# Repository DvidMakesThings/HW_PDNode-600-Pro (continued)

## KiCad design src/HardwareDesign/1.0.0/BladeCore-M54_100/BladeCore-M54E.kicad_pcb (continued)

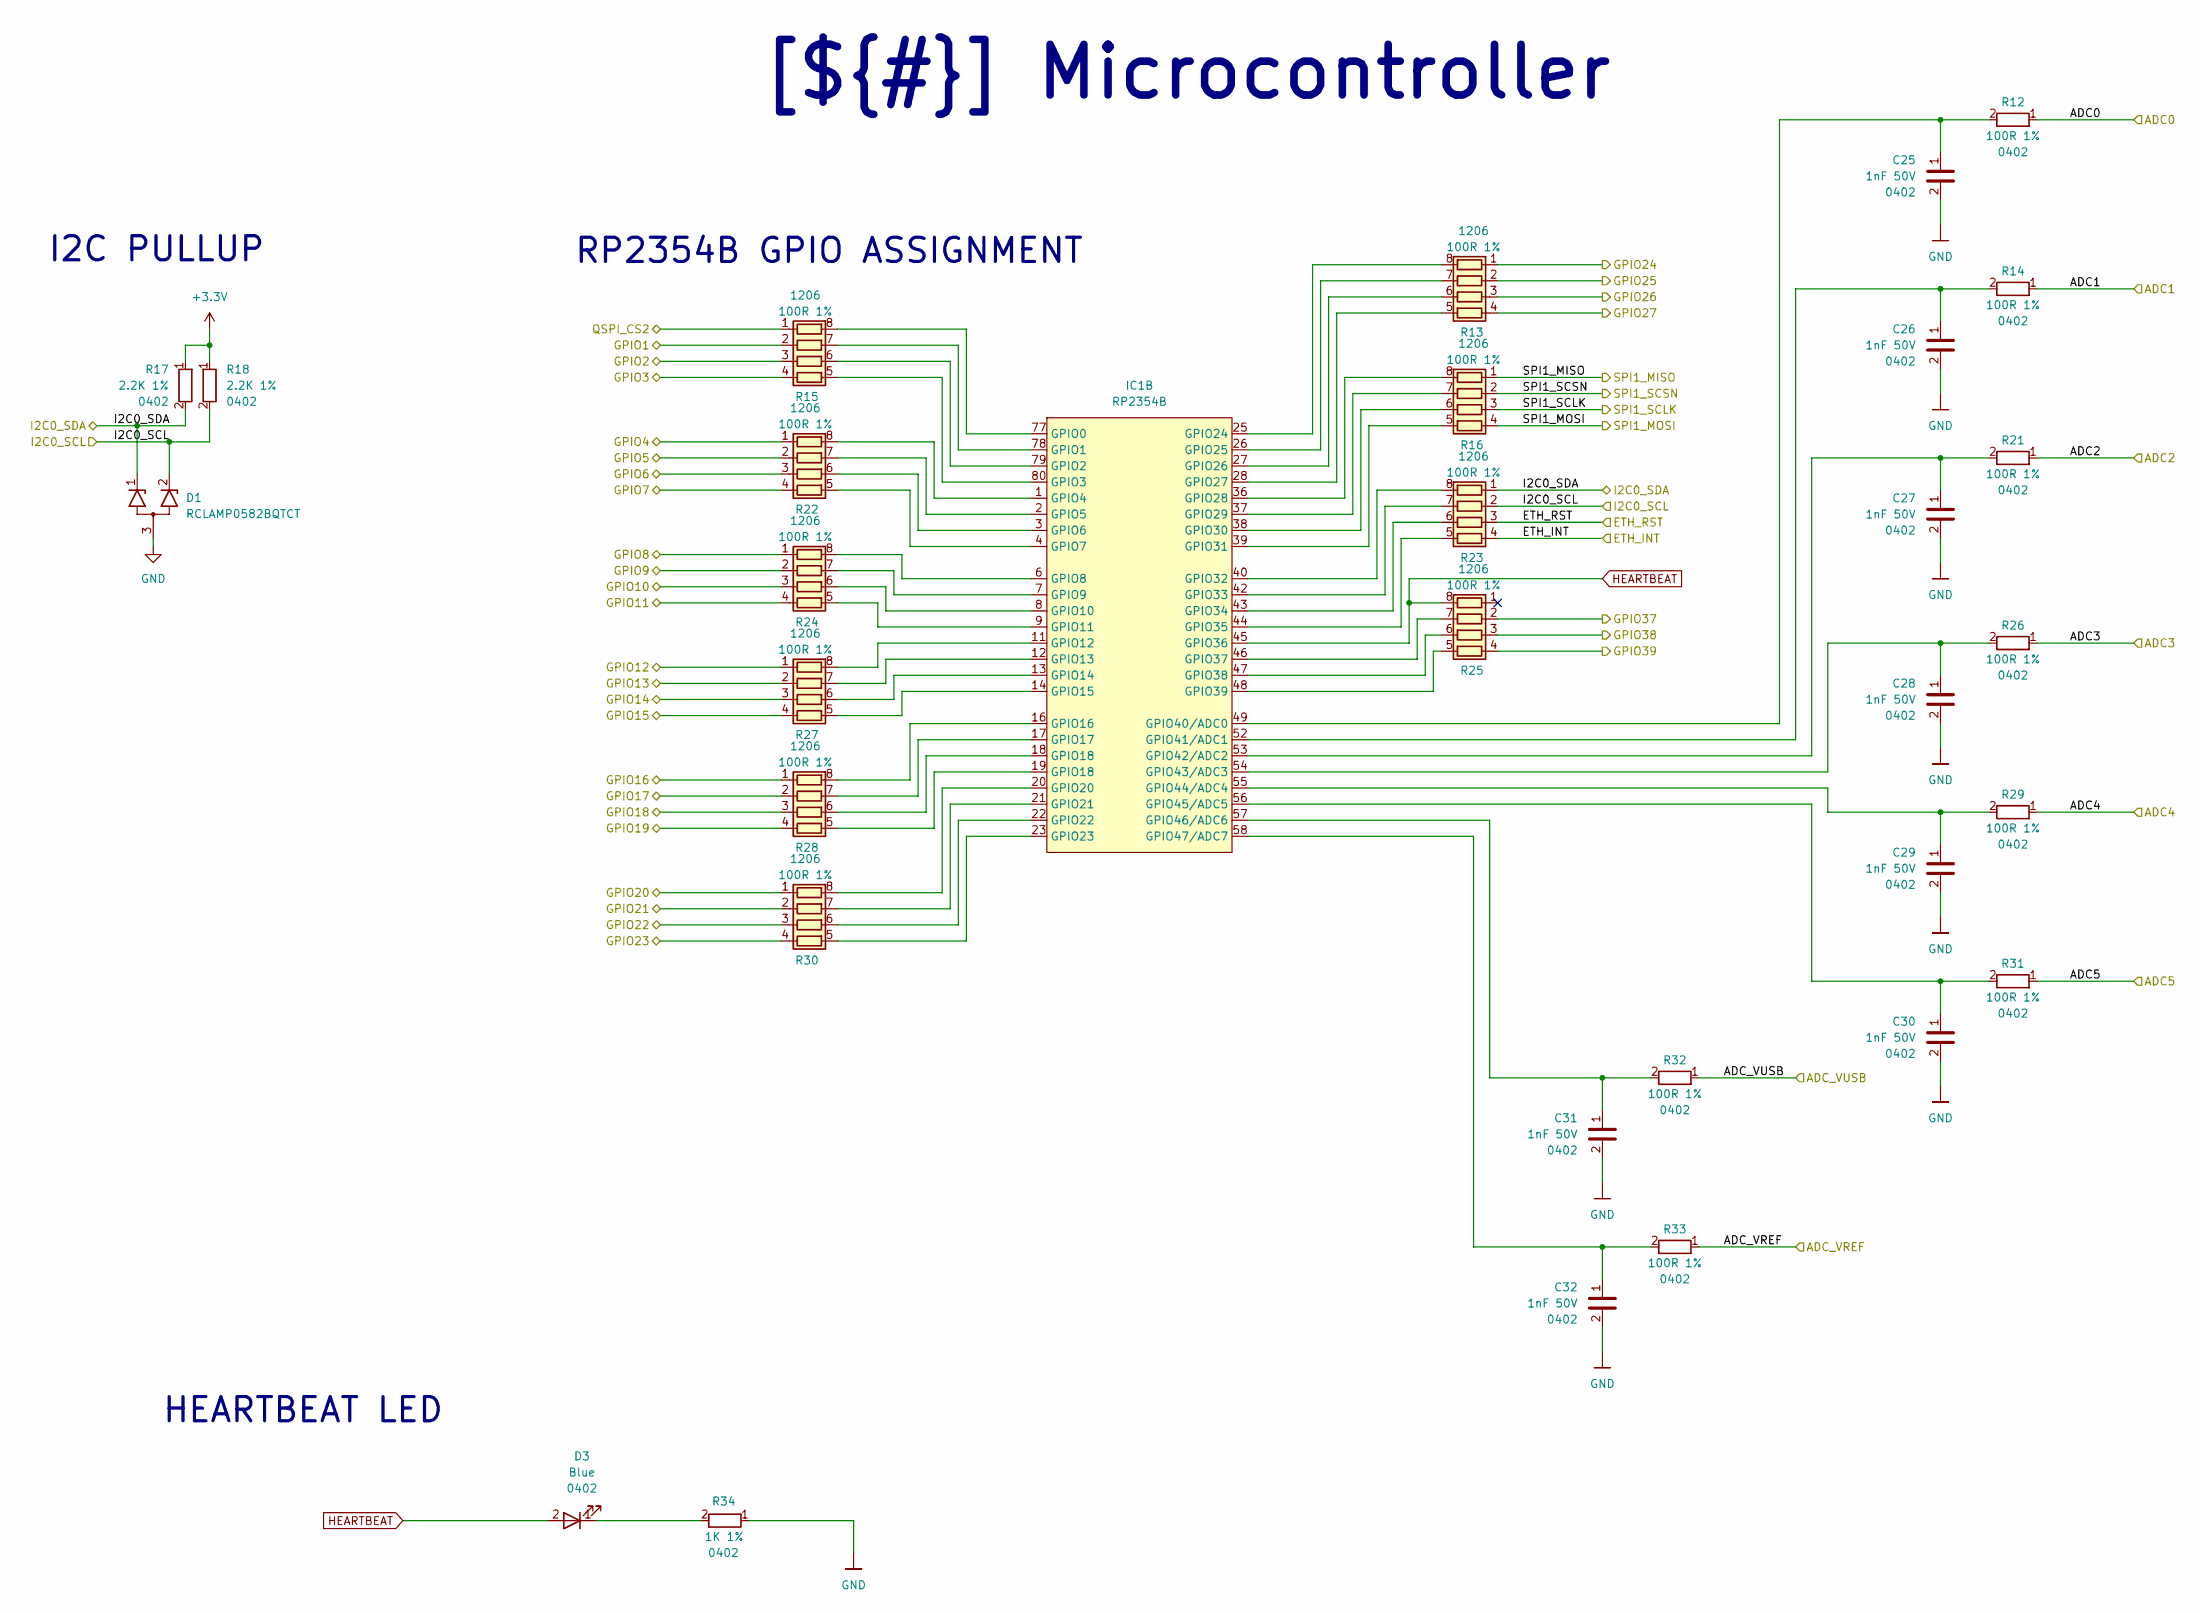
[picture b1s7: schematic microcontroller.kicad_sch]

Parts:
C25, C26, C27, C28, C29, C30, C31, C32: 1nF 50V; C_0402_1005Metric; LCSC_PART C14442
D1: RCLAMP0582BQTCT; SOT-416; MPN RCLAMP0582BQTCT; LCSC_PART C841193
D3: Blue; LED_0402_1005Metric; MPN XL-1005UBC; LCSC_PART C22355736
IC1: RP2354B; QFN80_10x10; MPN RP2354B; LCSC_PART C39843328
R12, R14, R21, R26, R29, R31, R32, R33: 100R 1%; R_0402_1005Metric; LCSC_PART C25076
R13, R15, R16, R22, R23, R24, R25, R27, R28, R30: 100R 1%; R_Array_Convex_4x0603; MPN YC164-FR-07100RL; LCSC_PART C136838
R17, R18: 2.2K 1%; R_0402_1005Metric; LCSC_PART C25879
R34: 1K 1%; R_0402_1005Metric; LCSC_PART C11702

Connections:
+3.3V: R17.1, R18.1; also elsewhere on the board
/Project Architecture/ADC0: R12.1; also elsewhere on the board
/Project Architecture/ADC1: R14.1; also elsewhere on the board
/Project Architecture/ADC2: R21.1; also elsewhere on the board
/Project Architecture/ADC3: R26.1; also elsewhere on the board
/Project Architecture/ADC4: R29.1; also elsewhere on the board
/Project Architecture/ADC5: R31.1; also elsewhere on the board
/Project Architecture/Ethernet Interface/ETH_INT: R23.4 (R14); also elsewhere on the board
/Project Architecture/Ethernet Interface/ETH_RST: R23.3 (R13); also elsewhere on the board
/Project Architecture/Ethernet Interface/SPI1_MISO: R16.1 (R11); also elsewhere on the board
/Project Architecture/Ethernet Interface/SPI1_MOSI: R16.4 (R14); also elsewhere on the board
/Project Architecture/Ethernet Interface/SPI1_SCLK: R16.3 (R13); also elsewhere on the board
/Project Architecture/Ethernet Interface/SPI1_SCSN: R16.2 (R12); also elsewhere on the board
/Project Architecture/GPIO0: R15.1 (R11); also elsewhere on the board
/Project Architecture/GPIO1: R15.2 (R12); also elsewhere on the board
/Project Architecture/GPIO2: R15.3 (R13); also elsewhere on the board
/Project Architecture/GPIO3: R15.4 (R14); also elsewhere on the board
/Project Architecture/GPIO4: R22.1 (R11); also elsewhere on the board
/Project Architecture/GPIO5: R22.2 (R12); also elsewhere on the board
/Project Architecture/GPIO6: R22.3 (R13); also elsewhere on the board
/Project Architecture/GPIO7: R22.4 (R14); also elsewhere on the board
/Project Architecture/GPIO8: R24.1 (R11); also elsewhere on the board
/Project Architecture/GPIO9: R24.2 (R12); also elsewhere on the board
/Project Architecture/GPIO10: R24.3 (R13); also elsewhere on the board
/Project Architecture/GPIO11: R24.4 (R14); also elsewhere on the board
/Project Architecture/GPIO12: R27.1 (R11); also elsewhere on the board
/Project Architecture/GPIO13: R27.2 (R12); also elsewhere on the board
/Project Architecture/GPIO14: R27.3 (R13); also elsewhere on the board
/Project Architecture/GPIO15: R27.4 (R14); also elsewhere on the board
/Project Architecture/GPIO16: R28.1 (R11); also elsewhere on the board
/Project Architecture/GPIO17: R28.2 (R12); also elsewhere on the board
/Project Architecture/GPIO18: R28.3 (R13); also elsewhere on the board
/Project Architecture/GPIO19: R28.4 (R14); also elsewhere on the board
/Project Architecture/GPIO20: R30.1 (R11); also elsewhere on the board
/Project Architecture/GPIO21: R30.2 (R12); also elsewhere on the board
/Project Architecture/GPIO22: R30.3 (R13); also elsewhere on the board
/Project Architecture/GPIO23: R30.4 (R14); also elsewhere on the board
/Project Architecture/GPIO24: R13.1 (R11); also elsewhere on the board
/Project Architecture/GPIO25: R13.2 (R12); also elsewhere on the board
/Project Architecture/GPIO26: R13.3 (R13); also elsewhere on the board
/Project Architecture/GPIO27: R13.4 (R14); also elsewhere on the board
/Project Architecture/Microcontroller Peripherals/ADC_VREF: R33.1; also elsewhere on the board
/Project Architecture/Microcontroller Peripherals/I2C0_SCL: D1.2 (K2), R18.2, R23.2 (R12); also elsewhere on the board
/Project Architecture/Microcontroller Peripherals/I2C0_SDA: D1.1 (K1), R17.2, R23.1 (R11); also elsewhere on the board
/Project Architecture/Microcontroller/ADC_VUSB: R32.1; also elsewhere on the board
/Project Architecture/Microcontroller/GPIO37: R25.2 (R12)
/Project Architecture/Microcontroller/GPIO38: R25.3 (R13)
/Project Architecture/Microcontroller/GPIO39: R25.4 (R14)
GND: C25.2, C26.2, C27.2, C28.2, C29.2, C30.2, C31.2, C32.2, D1.3 (A), R34.1; also elsewhere on the board
HEARTBEAT: D3.2, IC1.45 (GPIO36), R25.8 (R12)
unnamed: D3.1, R34.2
unnamed: IC1.77 (GPIO0), R15.8 (R12)
unnamed: IC1.78 (GPIO1), R15.7 (R22)
unnamed: IC1.79 (GPIO2), R15.6 (R23)
unnamed: IC1.80 (GPIO3), R15.5 (R24)
unnamed: IC1.1 (GPIO4), R22.8 (R12)
unnamed: IC1.2 (GPIO5), R22.7 (R22)
unnamed: IC1.3 (GPIO6), R22.6 (R23)
unnamed: IC1.4 (GPIO7), R22.5 (R24)
unnamed: IC1.6 (GPIO8), R24.8 (R12)
unnamed: IC1.7 (GPIO9), R24.7 (R22)
unnamed: IC1.8 (GPIO10), R24.6 (R23)
unnamed: IC1.9 (GPIO11), R24.5 (R24)
unnamed: IC1.11 (GPIO12), R27.8 (R12)
unnamed: IC1.12 (GPIO13), R27.7 (R22)
unnamed: IC1.13 (GPIO14), R27.6 (R23)
unnamed: IC1.14 (GPIO15), R27.5 (R24)
unnamed: IC1.16 (GPIO16), R28.8 (R12)
unnamed: IC1.17 (GPIO17), R28.7 (R22)
unnamed: IC1.20 (GPIO20), R30.8 (R12)
unnamed: IC1.21 (GPIO21), R30.7 (R22)
unnamed: IC1.22 (GPIO22), R30.6 (R23)
unnamed: IC1.23 (GPIO23), R30.5 (R24)
unnamed: IC1.25 (GPIO24), R13.8 (R12)
unnamed: IC1.26 (GPIO25), R13.7 (R22)
unnamed: IC1.27 (GPIO26), R13.6 (R23)
unnamed: IC1.28 (GPIO27), R13.5 (R24)
unnamed: IC1.36 (GPIO28), R16.8 (R12)
unnamed: IC1.37 (GPIO29), R16.7 (R22)
unnamed: IC1.38 (GPIO30), R16.6 (R23)
unnamed: IC1.39 (GPIO31), R16.5 (R24)
unnamed: IC1.40 (GPIO32), R23.8 (R12)
unnamed: IC1.42 (GPIO33), R23.7 (R22)
unnamed: IC1.43 (GPIO34), R23.6 (R23)
unnamed: IC1.44 (GPIO35), R23.5 (R24)
unnamed: IC1.46 (GPIO37), R25.7 (R22)
unnamed: IC1.47 (GPIO38), R25.6 (R23)
unnamed: IC1.48 (GPIO39), R25.5 (R24)
unnamed: C25.1, IC1.49 (GPIO40/ADC0), R12.2
unnamed: C26.1, IC1.52 (GPIO41/ADC1), R14.2
unnamed: C27.1, IC1.53 (GPIO42/ADC2), R21.2
unnamed: C28.1, IC1.54 (GPIO43/ADC3), R26.2
unnamed: C29.1, IC1.55 (GPIO44/ADC4), R29.2
unnamed: C30.1, IC1.56 (GPIO45/ADC5), R31.2
unnamed: C31.1, IC1.57 (GPIO46/ADC6), R32.2
unnamed: C32.1, IC1.58 (GPIO47/ADC7), R33.2
unnamed: IC1.18 (GPIO18), R28.6 (R23)
unnamed: IC1.19 (GPIO18), R28.5 (R24)

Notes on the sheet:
I2C PULLUP
HEARTBEAT LED
RP2354B GPIO ASSIGNMENT
[${#}] ${TITLE}

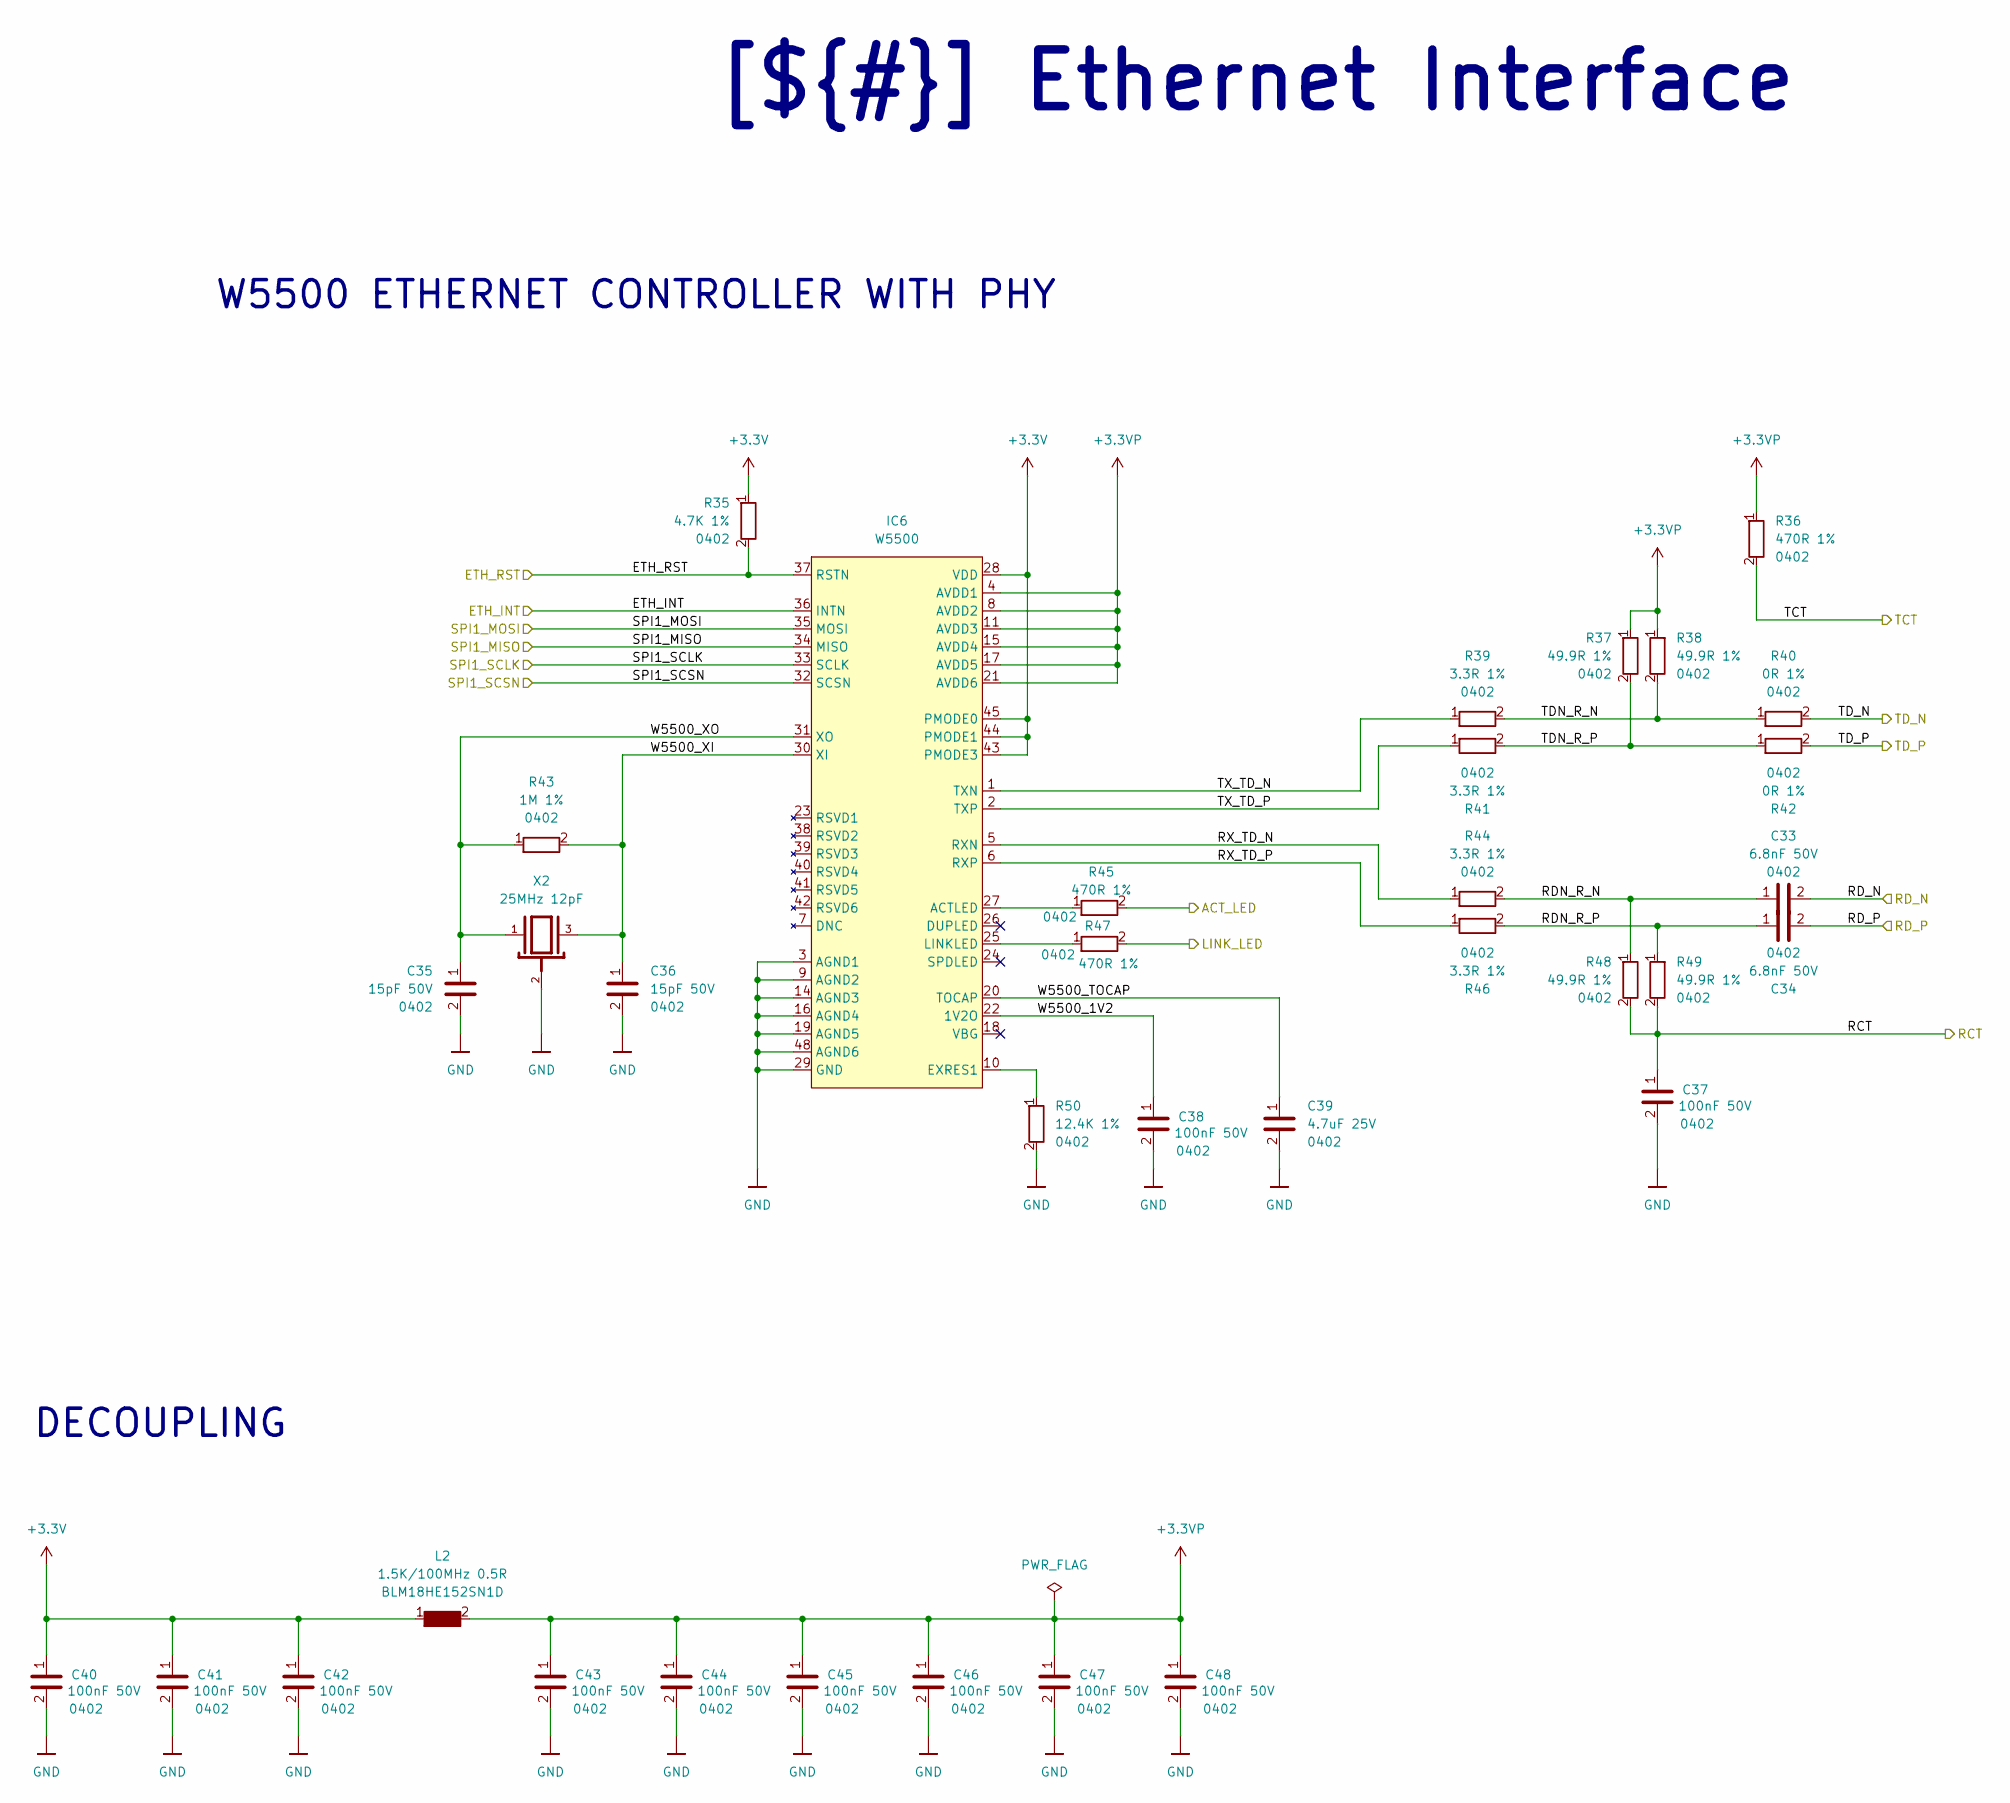
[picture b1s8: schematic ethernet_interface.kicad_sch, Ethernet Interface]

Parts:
C33, C34: 6.8nF 50V; C_0402_1005Metric; LCSC_PART C1542
C35, C36: 15pF 50V; C_0402_1005Metric; LCSC_PART C1548
C37, C38, C40, C41, C42, C43, C44, C45, C46, C47, C48: 100nF 50V; C_0402_1005Metric; LCSC_PART C307331
C39: 4.7uF 25V; C_0402_1005Metric; LCSC_PART C22367824
IC6: W5500; LQFP48_7x7; MPN W5500; LCSC_PART C32843
L2: 1.5K/100MHz 0.5R; R_0603_1608Metric; MPN BLM18HE152SN1D; LCSC_PART C82155
R35: 4.7K 1%; R_0402_1005Metric; LCSC_PART C25900
R36, R45, R47: 470R 1%; R_0402_1005Metric; LCSC_PART C25117
R37, R38, R48, R49: 49.9R 1%; R_0402_1005Metric; LCSC_PART C25120
R39, R41, R44, R46: 3.3R 1%; R_0402_1005Metric; LCSC_PART C270612
R40, R42: 0R 1%; R_0402_1005Metric; LCSC_PART C17168
R43: 1M 1%; R_0402_1005Metric; LCSC_PART C26083
R50: 12.4K 1%; R_0402_1005Metric; LCSC_PART C490814
X2: 25MHz 12pF; X3225; MPN X322525MOB4SI; LCSC_PART C9006

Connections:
+3.3V: C40.1, C41.1, C42.1, IC6.28 (VDD), IC6.43 (PMODE3), IC6.44 (PMODE1), IC6.45 (PMODE0), L2.1, R35.1; also elsewhere on the board
+3.3VP: C43.1, C44.1, C45.1, C46.1, C47.1, C48.1, IC6.4 (AVDD1), IC6.8 (AVDD2), IC6.11 (AVDD3), IC6.15 (AVDD4), IC6.17 (AVDD5), IC6.21 (AVDD6), L2.2, R36.1, R37.1, R38.1
/Project Architecture/ACT_LED: R45.2; also elsewhere on the board
/Project Architecture/Ethernet Interface/ETH_INT: IC6.36 (INTN); also elsewhere on the board
/Project Architecture/Ethernet Interface/ETH_RST: IC6.37 (RSTN), R35.2; also elsewhere on the board
/Project Architecture/Ethernet Interface/RDN_R_N: C33.1, R44.2, R48.1
/Project Architecture/Ethernet Interface/RDN_R_P: C34.1, R46.2, R49.1
/Project Architecture/Ethernet Interface/RX_TD_N: IC6.5 (RXN), R44.1
/Project Architecture/Ethernet Interface/RX_TD_P: IC6.6 (RXP), R46.1
/Project Architecture/Ethernet Interface/SPI1_MISO: IC6.34 (MISO); also elsewhere on the board
/Project Architecture/Ethernet Interface/SPI1_MOSI: IC6.35 (MOSI); also elsewhere on the board
/Project Architecture/Ethernet Interface/SPI1_SCLK: IC6.33 (SCLK); also elsewhere on the board
/Project Architecture/Ethernet Interface/SPI1_SCSN: IC6.32 (SCSN); also elsewhere on the board
/Project Architecture/Ethernet Interface/TDN_R_N: R38.2, R39.2, R40.1
/Project Architecture/Ethernet Interface/TDN_R_P: R37.2, R41.2, R42.1
/Project Architecture/Ethernet Interface/TX_TD_N: IC6.1 (TXN), R39.1
/Project Architecture/Ethernet Interface/TX_TD_P: IC6.2 (TXP), R41.1
/Project Architecture/Ethernet Interface/W5500_1V2: C38.1, IC6.22 (1V2O)
/Project Architecture/Ethernet Interface/W5500_TOCAP: C39.1, IC6.20 (TOCAP)
/Project Architecture/Ethernet Interface/W5500_XI: C36.1, IC6.30 (XI), R43.2, X2.3
/Project Architecture/Ethernet Interface/W5500_XO: C35.1, IC6.31 (XO), R43.1, X2.1
/Project Architecture/LINK_LED: R47.2; also elsewhere on the board
/Project Architecture/RCT: C37.1, R48.2, R49.2; also elsewhere on the board
/Project Architecture/RD_N: C33.2; also elsewhere on the board
/Project Architecture/RD_P: C34.2; also elsewhere on the board
/Project Architecture/TCT: R36.2; also elsewhere on the board
/Project Architecture/TD_N: R40.2; also elsewhere on the board
/Project Architecture/TD_P: R42.2; also elsewhere on the board
GND: C35.2, C36.2, C37.2, C38.2, C39.2, C40.2, C41.2, C42.2, C43.2, C44.2, C45.2, C46.2, C47.2, C48.2, IC6.3 (AGND1), IC6.9 (AGND2), IC6.14 (AGND3), IC6.16 (AGND4), IC6.19 (AGND5), IC6.29 (GND), IC6.48 (AGND6), R50.2, X2.2; also elsewhere on the board
unnamed: IC6.27 (ACTLED), R45.1
unnamed: IC6.10 (EXRES1), R50.1
unnamed: IC6.25 (LINKLED), R47.1

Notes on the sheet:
DECOUPLING
W5500 ETHERNET CONTROLLER WITH PHY
[${#}] ${TITLE}

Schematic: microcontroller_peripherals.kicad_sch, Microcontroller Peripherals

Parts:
C1, C2, C3, C4, C5, C7, C8, C9, C10, C13, C14, C15, C17, C18, C19, C21, C23: 100nF 50V; C_0402_1005Metric; LCSC_PART C307331
C6, C16: 4.7uF 25V; C_0402_1005Metric; LCSC_PART C22367824
C11, C12: 10pF 50V; C_0402_1005Metric; LCSC_PART C466222
C20, C22, C24: 4.7uF 10V; C_0402_1005Metric; LCSC_PART C368809
IC1: RP2354B; QFN80_10x10; MPN RP2354B; LCSC_PART C39843328
IC2: AT24C256C-XHL-T; TSSOP-8; MPN AT24C256C-XHL-T; LCSC_PART C33035
IC3: W25Q128JVPIQ; WSON8_6x5; MPN W25Q128JVPIQ; LCSC_PART C190862
IC4: MCP6001RT; SOT-23-5; MPN MCP6001RT-I/OT; LCSC_PART C154973
IC5: LM4040B30FTA; SOT-23; MPN LM4040B30FTA; LCSC_PART C460604
J2: SM03B-SRSS-TB; JST_SM03B-SRSS-TB_LF__SN_; MPN SM03B-SRSS-TB; LCSC_PART C160403
L1: 3.3uH 2.8A; 0805; MPN AOTA-B201610S3R3-101-T; LCSC_PART C42411119
R1, R8: 4.7K 1%; R_0402_1005Metric; LCSC_PART C25900
R2, R3, R4: 33R 1%; R_0402_1005Metric; LCSC_PART C25105
R5: 1K 1%; R_0402_1005Metric; LCSC_PART C11702
R6: 1K 1%; R_0402_1005Metric; LCSC_PART C11702; not fitted
R7: 27R 1%; R_0402_1005Metric; LCSC_PART C138021
R9: 27R 1%; R_0402_1005Metric; LCSC_PART C138021; not fitted
R10, R11: 10K 1%; R_0402_1005Metric; LCSC_PART C25744
SW1, SW2: B3U-1000P; SW_B3U-1000P; MPN B3U-1000P; LCSC_PART C231329
X1: 12MHz 10pF; X3225; MPN ABM8-272-T3; LCSC_PART C20625731

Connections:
+1V1: C13.1, C14.1, C15.1, C16.1, IC1.10 (DVDD1), IC1.32 (DVDD2), IC1.51 (DVDD3), IC1.65 (VREF_FB), L1.1
+3.3V: C1.1, C2.1, C3.1, C4.1, C5.1, C7.1, C8.1, C9.1, C10.1, C17.1, C18.1, C20.1, IC1.5 (IOVDD1), IC1.15 (IOVDD2), IC1.24 (IOVDD3), IC1.29 (IOVDD4), IC1.41 (IOVDD5), IC1.50 (IOVDD6), IC1.60 (IOVDD7), IC1.64 (VREG_IN), IC1.68 (USB_OTP_VDD), IC1.69 (QSPI_IOVDD), IC1.76 (IOVDD8), IC2.8 (VCC), IC3.8 (VCC), R1.1, R2.1, R6.1, R7.2, R8.1, R9.2; also elsewhere on the board
/Project Architecture/Microcontroller Peripherals/ADC_VREF: R10.2, R11.1; also elsewhere on the board
/Project Architecture/Microcontroller Peripherals/I2C0_SCL: IC2.6 (SCL); also elsewhere on the board
/Project Architecture/Microcontroller Peripherals/I2C0_SDA: IC2.5 (SDA); also elsewhere on the board
/Project Architecture/Microcontroller Peripherals/RP_D+: IC1.67 (USB_DP), R4.2
/Project Architecture/Microcontroller Peripherals/RP_D-: IC1.66 (USB_DM), R3.1
/Project Architecture/Microcontroller Peripherals/SWCLK: IC1.33 (SWCLK), J2.3 (SWDAT)
/Project Architecture/Microcontroller Peripherals/SWDIO: IC1.34 (SWDIO), J2.1 (SWCLK)
/Project Architecture/Microcontroller Peripherals/VREF_IN: C21.1, C22.1, IC4.3 (+), IC5.1 (K), R8.2
/Project Architecture/Microcontroller Peripherals/VREG_AVDD: C6.1, IC1.61 (VREG_AVDD), R2.2
/Project Architecture/Microcontroller Peripherals/VREG_LX: IC1.63 (VREG_LC), L1.2
/Project Architecture/Microcontroller Peripherals/XIN: C12.1, IC1.30 (XIN), X1.3
/Project Architecture/Microcontroller Peripherals/XO: C11.1, R5.2, X1.1
/Project Architecture/Microcontroller Peripherals/XOUT: IC1.31 (XOUT), R5.1
/Project Architecture/USB Interface and Power/USB_RP_D+: R4.1; also elsewhere on the board
/Project Architecture/USB Interface and Power/USB_RP_D-: R3.2; also elsewhere on the board
GND: C1.2, C2.2, C3.2, C4.2, C5.2, C6.2, C7.2, C8.2, C9.2, C10.2, C11.2, C12.2, C13.2, C14.2, C15.2, C16.2, C17.2, C18.2, C19.2, C20.2, C21.2, C22.2, C23.2, C24.2, IC1.62 (VREG_PGND), IC1.81 (GND), IC2.1 (A0), IC2.2 (A1), IC2.3 (A2), IC2.4 (GND), IC2.7 (WP), IC3.4 (GND), IC3.9 (PAD), IC4.5 (V-), IC5.2 (A), J2.2 (GND), J2.S1 (SHIELD), J2.S2 (SHIELD), R11.2, SW1.2, SW2.2, X1.2; also elsewhere on the board
unnamed: C19.1, IC4.2 (V+), R7.1
QSPI_SCLK: IC1.71 (QSPI_SCLK), IC3.6 (CLK)
QSPI_SD0: IC1.72 (QSPI_SD0), IC3.5 (DI(IO0))
QSPI_SD1: IC1.74 (QSPI_SD1), IC3.2 (DO(IO1))
QSPI_SD2: IC1.73 (QSPI_SD2), IC3.3 (nWP(IO2))
QSPI_SD3: IC1.70 (QSPI_SD3), IC3.7 (nRST(IO3))
QSPI_SS: IC1.75 (QSPI_SS), IC3.1 (nCS), R6.2, SW1.1
RESET: IC1.35 (RUN), R1.2, SW2.1
VREF_OUT: C23.1, C24.1, IC1.59 (ADC_AVDD), IC4.1, IC4.4 (-), R9.1, R10.1

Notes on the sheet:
EXTERNAL EEPROM
PUSHBUTTONS
EXTERNAL FLASH
RP2354B MICROCONTROLLER
HW Design Guide: RC filter of 33Ω and 4.7μF is adequate
HW Design Guide: recommended to use 100nF capacitor per power pin
3.0V ADC VOLTAGE REFERENCE
12MHz 10pF -> Assuming 5pF parasitics Csum = 10pF - 5pF = 5pF C1 = C2 = 5pF x 2 = 10pF
[${#}] ${TITLE}

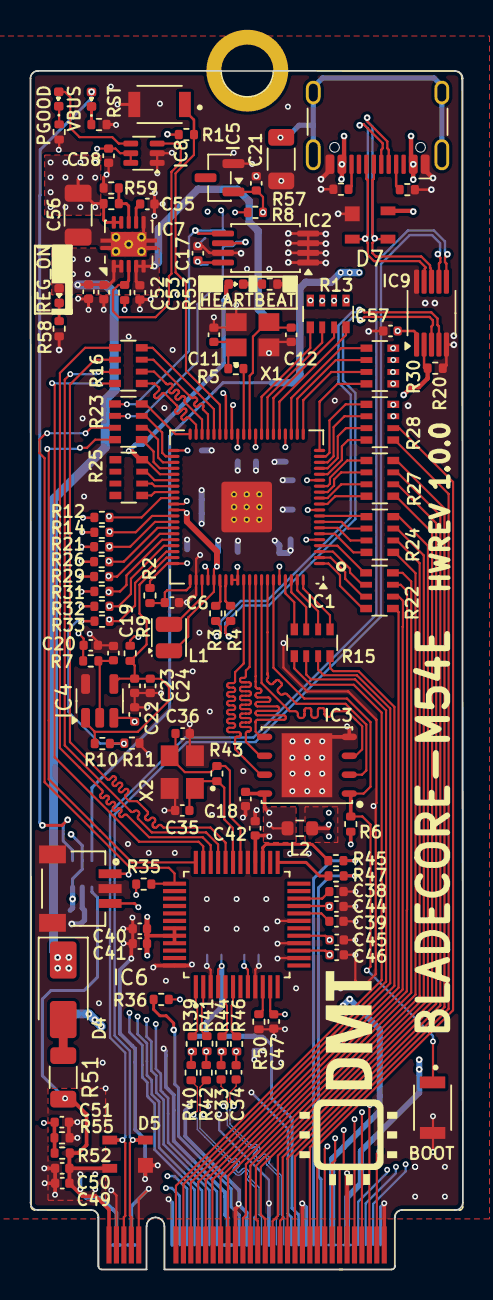
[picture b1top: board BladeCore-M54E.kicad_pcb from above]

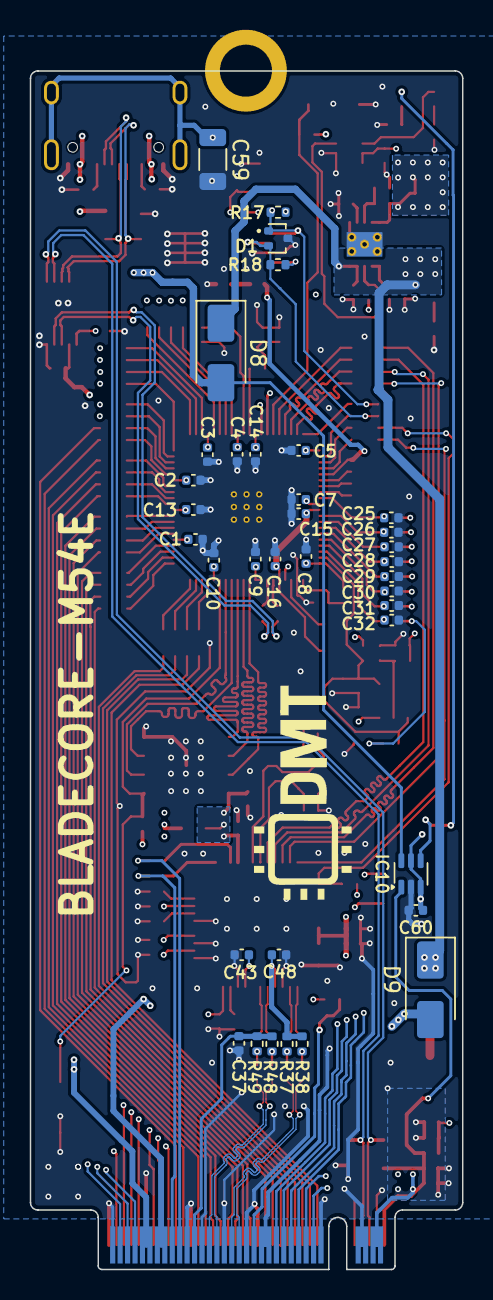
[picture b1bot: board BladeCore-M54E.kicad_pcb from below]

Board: 6 copper layers, 29.0 x 80.6 mm, 150 parts (36 on the bottom side), 161 nets.

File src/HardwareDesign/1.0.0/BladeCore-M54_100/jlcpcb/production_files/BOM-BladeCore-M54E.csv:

Comment,Designator,Footprint,LCSC,Quantity
0R 1%,"R40,R42",R_0402_1005Metric,C17168,2
0R 1%,R51,R_1206_3216Metric,C205296,1
1.5K/100MHz 0.5R,L2,R_0603_1608Metric,C82155,1
100R 1%,"R13,R15,R16,R22,R23,R24,R25,R27,R28,R30",R_Array_Convex_4x0603,C136838,10
100R 1%,"R12,R14,R21,R26,R29,R31,R32,R33",R_0402_1005Metric,C25076,8
100nF 50V,"C1,C10,C13,C14,C15,C17,C18,C19,C2,C21,C23,C3,C37,C38,C4,C40,C41,C42,C43,C44,C45,C46,C47,C48,C5,C51,C52,C57,C58,C60,C7,C8,C9",C_0402_1005Metric,C307331,33
10K 1%,"R10,R11,R53",R_0402_1005Metric,C25744,3
10pF 50V,"C11,C12",C_0402_1005Metric,C466222,2
10uF 50V,C56,C_1206_3216Metric,C13585,1
12.4K 1%,R50,R_0402_1005Metric,C490814,1
12MHz 10pF,X1,X3225,C20625731,1
15pF 50V,"C35,C36",C_0402_1005Metric,C1548,2
1K 1%,"R34,R5,R58,R60,R61",R_0402_1005Metric,C11702,5
1M 1%,R57,R_1206_3216Metric,C17927,1
1M 1%,R43,R_0402_1005Metric,C26083,1
1nF 2kV,C59,C_1206_3216Metric,C173242,1
1nF 50V,"C25,C26,C27,C28,C29,C30,C31,C32",C_0402_1005Metric,C14442,8
1uF 50V,C53,C_0402_1005Metric,C1518208,1
2.2K 1%,"R17,R18",R_0402_1005Metric,C25879,2
2.2nF 50V,C55,C_0402_1005Metric,C106861,1
2.4K 1%,R59,R_0402_1005Metric,C25882,1
25MHz 12pF,X2,X3225,C9006,1
27R 1%,R7,R_0402_1005Metric,C138021,1
3.3R 1%,"R39,R41,R44,R46",R_0402_1005Metric,C270612,4
3.3uH 2.8A,L1,0805,C42411119,1
33R 1%,"R2,R3,R4",R_0402_1005Metric,C25105,3
4.7K 1%,"R1,R35,R8",R_0402_1005Metric,C25900,3
4.7uF 10V,"C20,C22,C24",C_0402_1005Metric,C368809,3
4.7uF 25V,"C16,C39,C49,C50,C54,C6",C_0402_1005Metric,C22367824,6
470R 1%,"R36,R45,R47",R_0402_1005Metric,C25117,3
49.9R 1%,"R37,R38,R48,R49",R_0402_1005Metric,C25120,4
5.1K 1%,"R19,R20,R52,R55,R56",R_0402_1005Metric,C25905,5
6.8nF 50V,"C33,C34",C_0402_1005Metric,C1542,2
7.5K 1%,R54,R_0402_1005Metric,C25918,1
AT24C256C-XHL-T,IC2,TSSOP-8,C33035,1
B3U-1000P,"SW1,SW2",SW_B3U-1000P,C231329,2
Blue,D3,LED_0402_1005Metric,C22355736,1
FSUSB42MUX,IC9,MSOP-10_3x3mm_P0.5mm,C11355,1
Green,"D10,D11,D6",LED_0402_1005Metric,C965793,3
LM4040B30FTA,IC5,SOT-23,C460604,1
MCP6001RT,IC4,SOT-23-5,C154973,1
RCLAMP0582BQTCT,D1,SOT-416,C841193,1
RP2354B,IC1,QFN80_10x10,C39843328,1
SM03B-SRSS-TB,J2,JST_SM03B-SRSS-TB_LF__SN_,C160403,1
SN74LVC1G97QDCKRQ1,"IC10,IC8",SOT-363_SC-70-6,C179911,2
SP0503BAHTG,"D5,D7",SOT143,C3040626,2
TPS74801DRCT,IC7,VSON-10-1EP_3x3mm_P0.5mm_EP1.65x2.4mm_ThermalVias,C882845,1
USB-TYPE-C-018,J3,USB_C_Receptacle_HCTL_HC-TYPE-C-16P-01A,C2927038,1
W25Q128JVPIQ,IC3,WSON8_6x5,C190862,1
W5500,IC6,LQFP48_7x7,C32843,1
